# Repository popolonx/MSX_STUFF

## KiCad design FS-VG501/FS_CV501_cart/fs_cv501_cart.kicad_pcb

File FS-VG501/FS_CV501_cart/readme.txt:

kicad files for CV501 cart part.

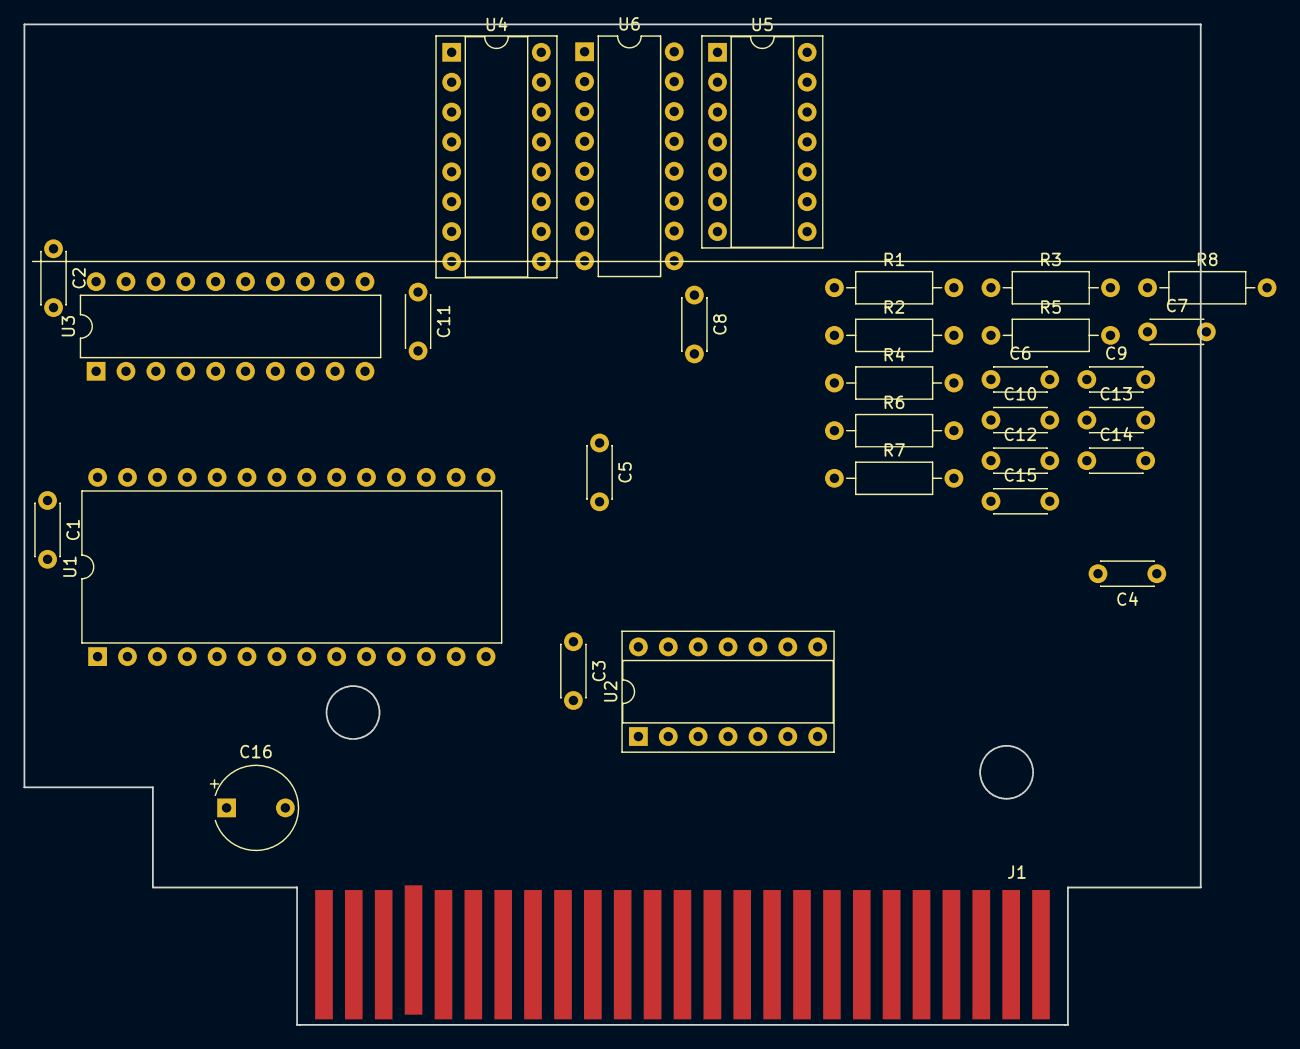
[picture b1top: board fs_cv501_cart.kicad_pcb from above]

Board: 2 copper layers, 100.0 x 85.0 mm, 31 parts (0 on the bottom side), 47 nets, no tracks yet.

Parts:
C1, C2, C3, C4, C5, C8, C11: 100nF; C_Disc_D4.3mm_W1.9mm_P5.00mm
C6, C7, C9, C10, C12, C13, C14, C15: 22p; C_Disc_D4.3mm_W1.9mm_P5.00mm
C16: 100uF; CP_Radial_Tantal_D7.0mm_P5.00mm
J1: Conn_02x25_Odd_Even; msx_cartridge
R1, R2, R3, R4, R5, R6, R7, R8: 1K; R_Axial_DIN0207_L6.3mm_D2.5mm_P10.16mm_Horizontal
U1: TMM27256D-25; DIP-28_W15.24mm
U2: 74LS30; DIP-14_W7.62mm_Socket
U3: 74LS245; DIP-20_W7.62mm
U4: 74LS138; DIP-16_W7.62mm_Socket
U5: 74LS08; DIP-14_W7.62mm_Socket
U6: 74LS367; DIP-16_W7.62mm

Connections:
5V: C1.1, C2.1, C3.1, C4.1, C5.1, C8.1, C11.1, C16.1, J1.45, J1.47, R1.1, R2.1, R3.1, R4.1, R5.1, R6.1, R7.1, R8.1, U1.1, U1.28, U2.14, U3.20, U4.6, U4.16, U5.14, U6.16
A0: J1.28, U1.10, U6.12
A1: J1.27, U1.9, U6.6
A2: J1.30, U1.8
A3: J1.29, U1.7
A4: J1.32, U1.6
A5: J1.31, U1.5
A6: J1.22, U1.4, U2.12
A7: J1.21, U1.3, U2.11
A8: J1.24, U1.25, U2.6
A9: J1.17, U1.24, U2.5
A10: J1.20, U1.21, U2.4
A11: J1.19, U1.23, U2.3
A12: J1.23, U1.2, U2.2
A13: J1.26, U1.26, U2.1
A14: J1.25, U1.27, U4.2
A15: J1.18, U4.3
D0: J1.34, U1.11, U3.2
D1: J1.33, U1.12, U3.3
D2: J1.36, U1.13, U3.4
D3: J1.35, U1.15, U3.5
D4: J1.38, U1.16, U3.6
D5: J1.37, U1.17, U3.7
D6: J1.40, U1.18, U3.8
D7: J1.39, U1.19, U3.9
DB0_PIN1: C6.1, R1.2, U3.18
DB1_PIN2: C7.1, R2.2, U3.17
DB2_PIN3: C9.1, R3.2, U3.16
DB3_PIN4: C10.1, R4.2, U3.15
DB4_PIN5: C12.1, R5.2, U3.14
DB5_PIN6: C13.1, R6.2, U3.13
DB6_PIN7: C14.1, R7.2, U3.12
DB7_PIN8: C15.1, R8.2, U3.11
GND: C1.2, C2.2, C3.2, C4.2, C5.2, C6.2, C7.2, C8.2, C9.2, C10.2, C11.2, C12.2, C13.2, C14.2, C15.2, C16.2, J1.41, J1.43, U1.14, U2.7, U3.10, U4.4, U4.8, U5.7, U6.1, U6.8, U6.15
unnamed: J1.44, J1.46
unnamed: U2.8, U4.1
unnamed: U4.10, U5.2
unnamed: U4.11, U5.4, U6.10
unnamed: U4.12, U5.1
unnamed: U4.13, U5.5, U6.2
_CS12: J1.3, U1.20
_RD: J1.14, U6.4
_RDB_PIN11: U3.1, U6.5
_ROMOE: U1.22, U5.3
_SLTSL: J1.4, U4.5
_SWITCH_ENABLE: U3.19, U5.6
_WR: J1.13, U6.14

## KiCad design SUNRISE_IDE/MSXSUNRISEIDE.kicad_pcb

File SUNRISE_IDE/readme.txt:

sunrise ide module schematics, original can be found from msxpro.com

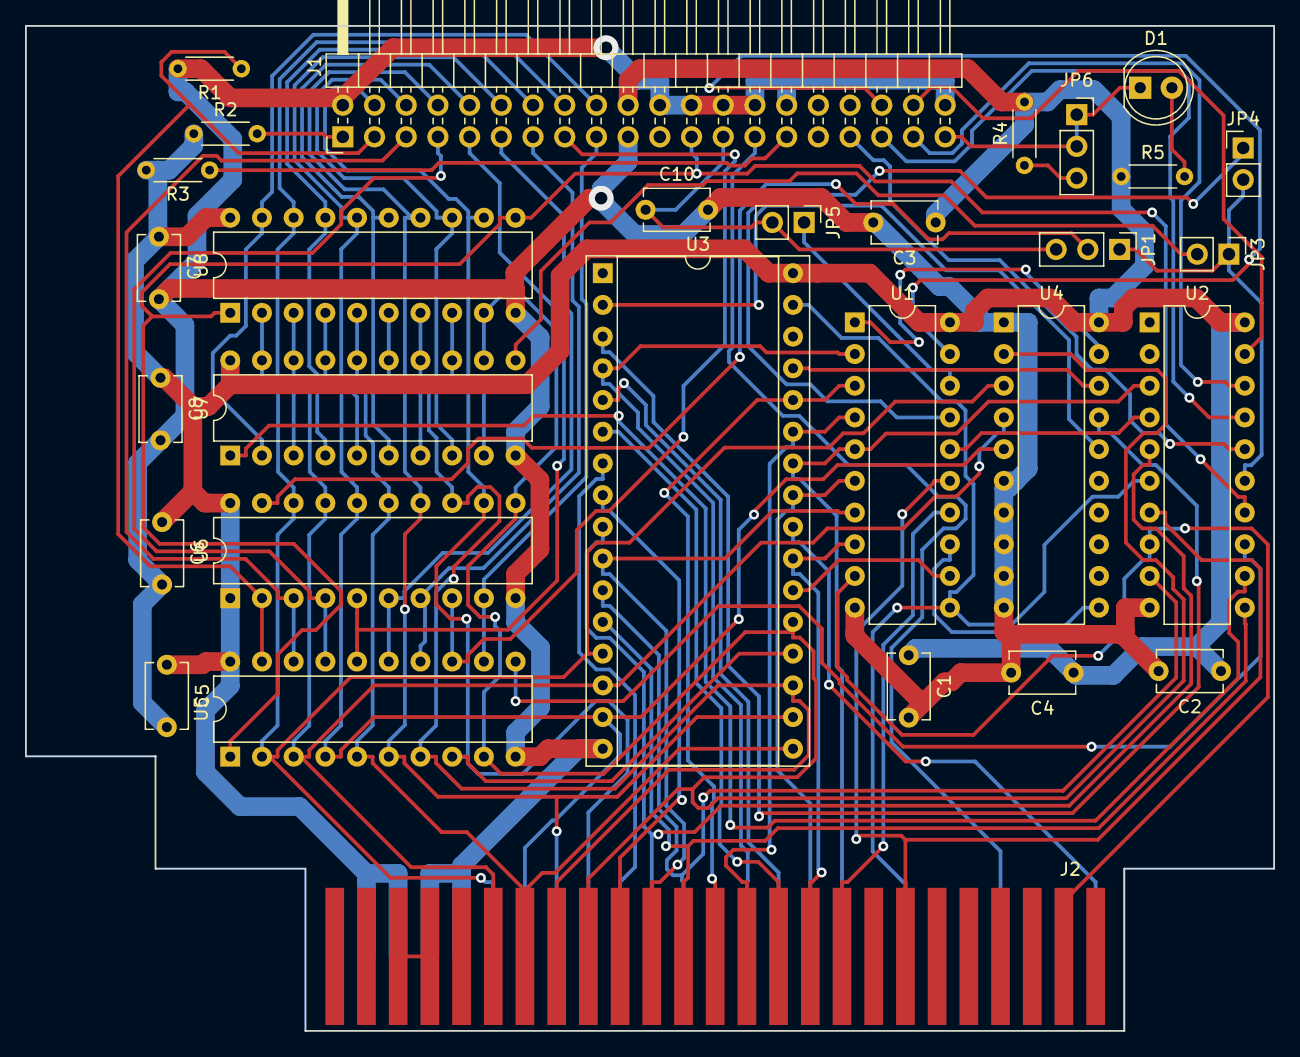
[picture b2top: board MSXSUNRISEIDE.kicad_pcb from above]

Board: 2 copper layers, 100.0 x 80.5 mm, 30 parts (0 on the bottom side), 73 nets.

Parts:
C1, C2, C3, C4, C5: 0.1 uF; C_Disc_D5.1mm_W3.2mm_P5.00mm
C6, C7, C8: 0.1uF; C_Disc_D5.1mm_W3.2mm_P5.00mm
C10: 470pF; C_Disc_D5.1mm_W3.2mm_P5.00mm
D1: LED; LED_D5.0mm
J1: Conn_02x20_Odd_Even; PinHeader_2x20_P2.54mm_Horizontal
J2: Conn_02x25_Odd_Even; msx_cartridge
JP1: Jumper_3_Open; PinHeader_1x03_P2.54mm_Vertical
JP3, JP4, JP5: Jumper; PinHeader_1x02_P2.54mm_Vertical
JP6: Jumper_3_Open; PinSocket_1x03_P2.54mm_Vertical
R1, R3: 10K; R_Axial_DIN0204_L3.6mm_D1.6mm_P5.08mm_Horizontal
R2: 4K7; R_Axial_DIN0204_L3.6mm_D1.6mm_P5.08mm_Horizontal
R4: 330R; R_Axial_DIN0204_L3.6mm_D1.6mm_P5.08mm_Horizontal
R5: 680R; R_Axial_DIN0204_L3.6mm_D1.6mm_P5.08mm_Horizontal
U1, U2: GAL16V8; DIP-20_W7.62mm
U3: SST39SF040; DIP-32_W15.24mm_Socket
U4, U5, U6, U7, U8: 74LS573; DIP-20_W7.62mm

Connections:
A0: J2.28, U2.11, U3.12
A1: J2.27, U2.9, U3.11
A2: J2.30, U1.7, U3.10
A3: J2.29, U2.5, U3.9
A4: J2.32, U3.8
A5: J2.31, U3.7
A6: J2.22, U3.6
A7: J2.21, U3.5
A8: J2.24, U1.4, U3.27
A9: J2.17, U1.5, U2.3, U3.26
A10: J2.20, U1.8, U3.23
A11: J2.19, U1.6, U3.25
A12: J2.23, U1.2, U3.4
A13: J2.26, U1.3, U3.28
A15: J2.18, U1.14
ACTIVE_: D1.1, J1.39, JP6.1, JP6.2
CS1_: J2.1, U3.24
D0: J2.34, U3.21, U4.2, U5.9, U6.11, U7.12, U8.9
D1: J2.33, U3.20, U5.8, U6.12, U7.13, U8.8
D2: J2.36, U3.19, U5.7, U6.13, U7.14, U8.7
D3: J2.35, U3.18, U5.6, U6.14, U7.15, U8.6
D4: J2.38, U3.17, U5.5, U6.15, U7.16, U8.5
D5: J2.37, U3.15, U4.5, U5.4, U6.16, U7.17, U8.4
D6: J2.40, U3.14, U4.4, U5.3, U6.17, U7.18, U8.3
D7: J2.39, U3.13, U4.3, U5.2, U6.18, U7.19, U8.2
DA0: J1.35, U2.17
DA1: J1.33, U2.16
DA2: J1.36, U1.19
DD0: J1.17, U5.12, U6.9
DD1: J1.15, U5.13, U6.8
DD2: J1.13, U5.14, U6.7
DD3: J1.11, U5.15, U6.6
DD4: J1.9, U5.16, U6.5
DD5: J1.7, U5.17, U6.4
DD6: J1.5, U5.18, U6.3
DD7: J1.3, R1.1, U5.19, U6.2
DD8: J1.4, U7.9, U8.12
DD9: J1.6, U7.8, U8.13
DD10: J1.8, U7.7, U8.14
DD11: J1.10, U7.6, U8.15
DD12: J1.12, U7.5, U8.16
DD13: J1.14, U7.4, U8.17
DD14: J1.16, U7.3, U8.18
DD15: J1.18, U7.2, U8.19
D_LOW: JP1.2, U6.19
FLASH_EN_: U1.12, U3.22
GND: C1.2, C2.2, C3.2, C4.2, C5.2, C6.2, C7.2, C8.2, C10.2, J1.2, J1.19, J1.22, J1.24, J1.26, J1.28, J1.30, J1.40, J2.41, J2.43, R1.2, U1.10, U2.10, U3.16, U4.1, U4.6, U4.7, U4.8, U4.9, U4.10, U5.10, U6.10, U7.10, U8.10
IDE_CS0_: J1.37, U2.18
IDE_CS1_: J1.38, U2.19
IOR_: C10.1, J1.25, JP1.3, JP5.2
IOW_: J1.23, U2.14, U5.1, U8.1, U8.11
MA: U1.1, U4.19
MA14: U3.29, U4.18
MA15: U3.3, U4.17
MA16: U3.2, U4.16
NET00003: U2.13, U5.11
unnamed: D1.2, R5.2
unnamed: J1.1, R2.2
unnamed: J1.29, R3.1
unnamed: J2.44, J2.46
unnamed: JP1.1, JP3.1, JP4.2, U2.15
unnamed: JP3.2, U7.11
unnamed: JP4.1, U1.17
unnamed: JP5.1, U1.18
unnamed: JP6.3, R4.1
unnamed: U1.13, U4.11
unnamed: U1.16, U2.4
unnamed: U2.12, U7.1
RD_: J2.14, U1.15, U2.7
SLTSL_: J2.4, U1.9, U2.8
VCC: C1.1, C2.1, C3.1, C4.1, C5.1, C6.1, C7.1, C8.1, J1.20, J2.45, J2.47, R2.1, R3.2, R4.2, R5.1, U1.20, U2.20, U3.32, U4.20, U5.20, U6.1, U6.20, U7.20, U8.20
WAIT_: J1.27, J2.7
WR_: J2.13, U1.11, U2.6, U3.31

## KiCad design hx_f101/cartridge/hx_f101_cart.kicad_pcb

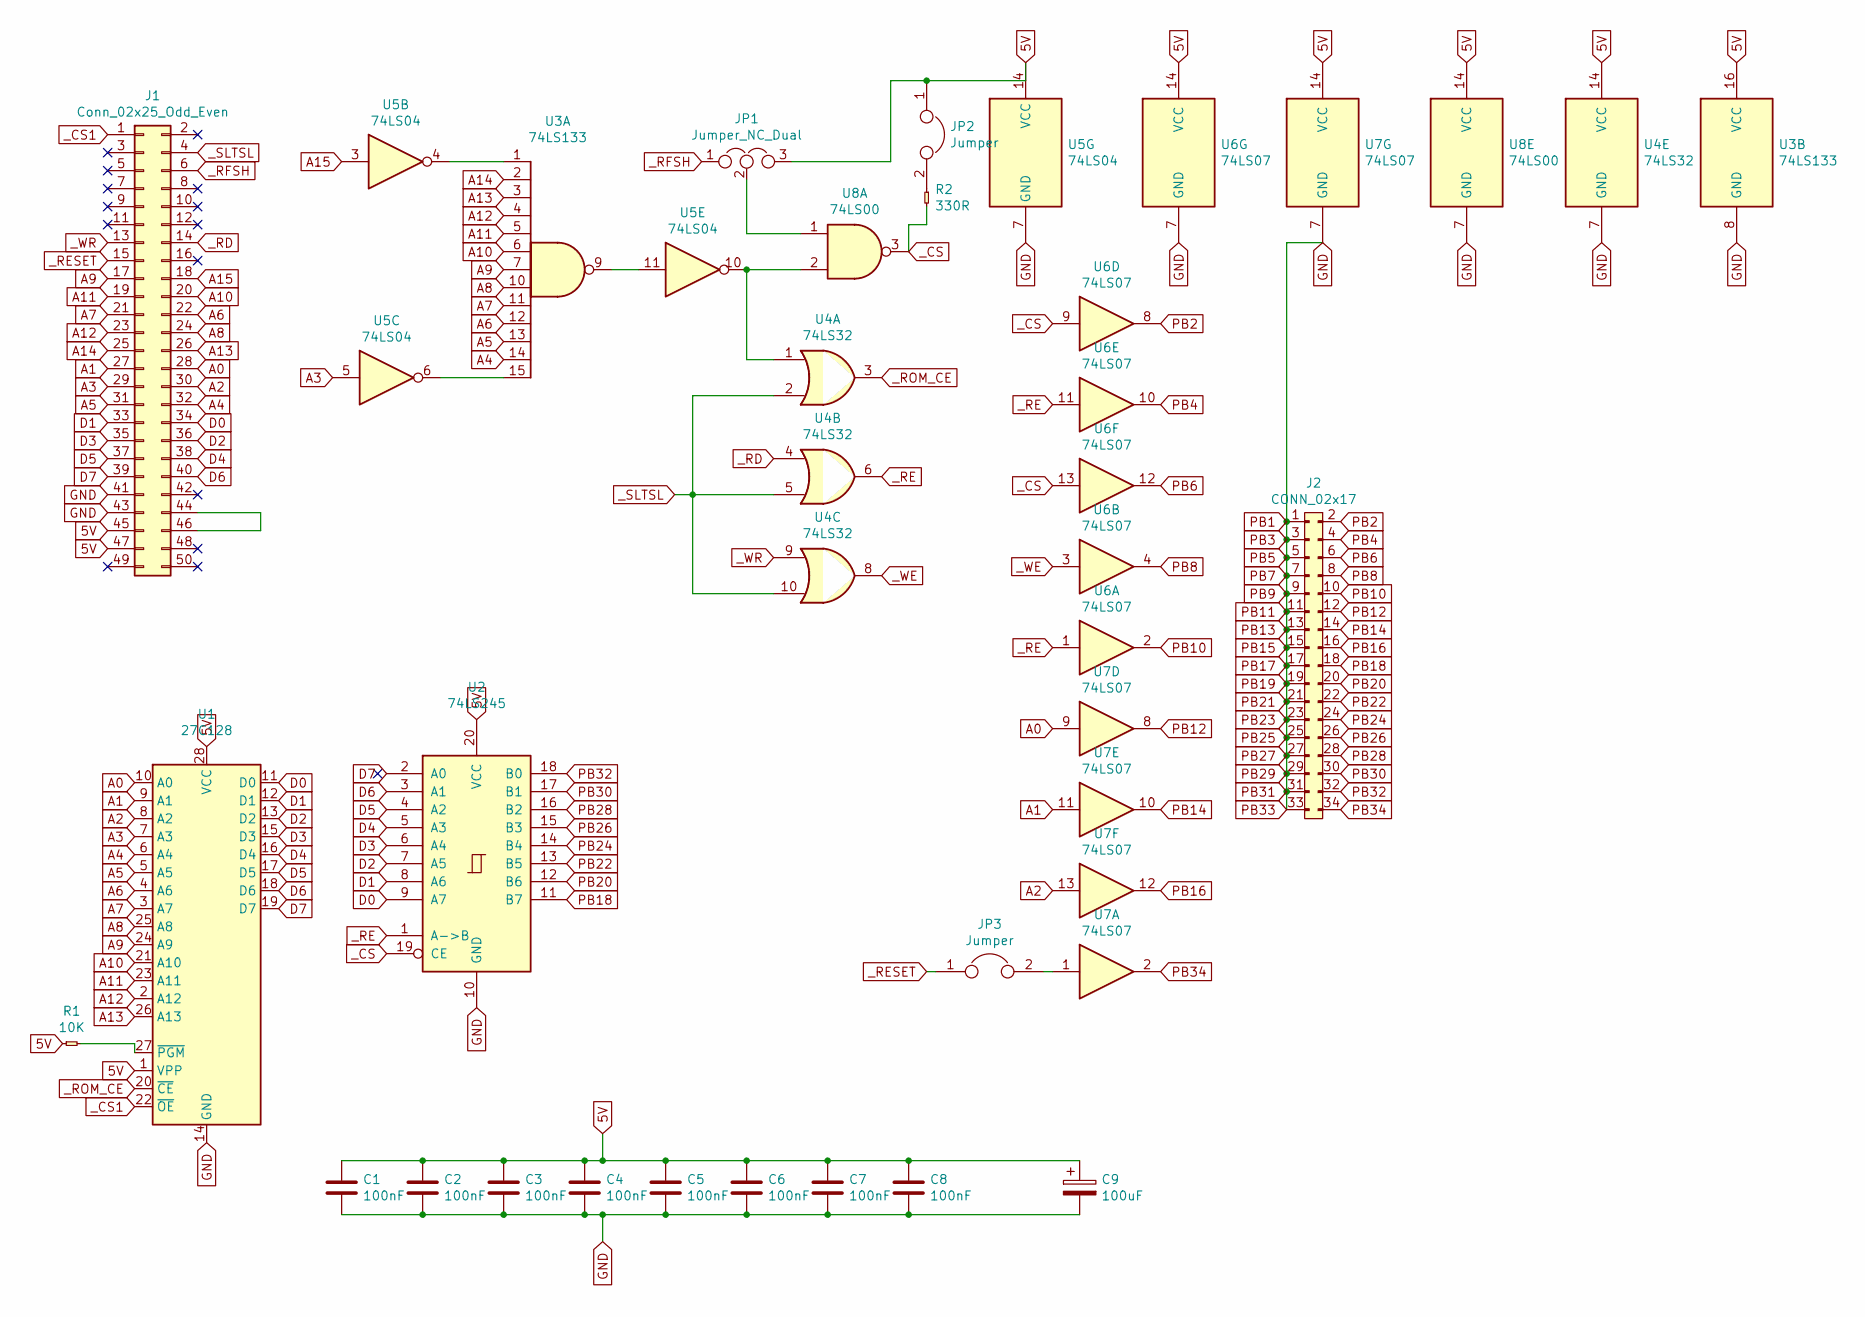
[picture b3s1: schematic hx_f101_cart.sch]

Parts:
C1, C2, C3, C4, C5, C6, C7, C8: 100nF; C_Disc_D4.3mm_W1.9mm_P5.00mm
C9: 100uF; CP_Radial_Tantal_D7.0mm_P5.00mm
J1: Conn_02x25_Odd_Even; msx_cartridge
J2: CONN_02x17; PinHeader_2x17_P2.54mm_Vertical
JP1: Jumper_NC_Dual; PinHeader_1x03_P2.54mm_Vertical
JP2, JP3: Jumper; PinHeader_1x02_P2.54mm_Vertical
R1: 10K; R_Axial_DIN0207_L6.3mm_D2.5mm_P10.16mm_Horizontal
R2: 330R; R_Axial_DIN0207_L6.3mm_D2.5mm_P10.16mm_Horizontal
U1: 27C128; DIP-28_W15.24mm
U2: 74LS245; DIP-20_W7.62mm
U3: 74LS133; DIP-16_W7.62mm
U4: 74LS32; DIP-14_W7.62mm
U5: 74LS04; DIP-14_W7.62mm
U6, U7: 74LS07; DIP-14_W7.62mm
U8: 74LS00; DIP-14_W7.62mm

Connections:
5V: C1.1, C2.1, C3.1, C4.1, C5.1, C6.1, C7.1, C8.1, C9.1, J1.45, J1.47, JP1.3, JP2.1, R1.1, U1.1 (VPP), U1.28 (VCC), U2.20 (VCC), U3.16 (VCC), U4.14 (VCC), U5.14 (VCC), U6.14 (VCC), U7.14 (VCC), U8.14 (VCC)
A0: J1.28, U1.10 (A0), U7.9
A1: J1.27, U1.9 (A1), U7.11
A2: J1.30, U1.8 (A2), U7.13
A3: J1.29, U1.7 (A3), U5.5
A4: J1.32, U1.6 (A4), U3.14
A5: J1.31, U1.5 (A5), U3.13
A6: J1.22, U1.4 (A6), U3.12
A7: J1.21, U1.3 (A7), U3.11
A8: J1.24, U1.25 (A8), U3.10
A9: J1.17, U1.24 (A9), U3.7
A10: J1.20, U1.21 (A10), U3.6
A11: J1.19, U1.23 (A11), U3.5
A12: J1.23, U1.2 (A12), U3.4
A13: J1.26, U1.26 (A13), U3.3
A14: J1.25, U3.2
A15: J1.18, U5.3
D0: J1.34, U1.11 (D0), U2.9 (A7)
D1: J1.33, U1.12 (D1), U2.8 (A6)
D2: J1.36, U1.13 (D2), U2.7 (A5)
D3: J1.35, U1.15 (D3), U2.6 (A4)
D4: J1.38, U1.16 (D4), U2.5 (A3)
D5: J1.37, U1.17 (D5), U2.4 (A2)
D6: J1.40, U1.18 (D6), U2.3 (A1)
D7: J1.39, U1.19 (D7), U2.2 (A0)
GND: C1.2, C2.2, C3.2, C4.2, C5.2, C6.2, C7.2, C8.2, C9.2, J1.41, J1.43, J2.1, J2.3, J2.5, J2.7, J2.9, J2.11, J2.13, J2.15, J2.17, J2.19, J2.21, J2.23, J2.25, J2.27, J2.29, J2.31, J2.33, U1.14 (GND), U2.10 (GND), U3.8 (GND), U4.7 (GND), U5.7 (GND), U6.7 (GND), U7.7 (GND), U8.7 (GND)
unnamed: J1.44, J1.46
unnamed: JP1.2, U8.1
unnamed: JP2.2, R2.1
unnamed: JP3.2, U7.1
unnamed: R1.2, U1.27 (~PGM)
unnamed: U3.1, U5.4
unnamed: U3.9, U5.11
unnamed: U3.15, U5.6
unnamed: U4.1, U5.10, U8.2
PB2: J2.2, U6.8
PB4: J2.4, U6.10
PB6: J2.6, U6.12
PB8: J2.8, U6.4
PB10: J2.10, U6.2
PB12: J2.12, U7.8
PB14: J2.14, U7.10
PB16: J2.16, U7.12
PB18: J2.18, U2.11 (B7)
PB20: J2.20, U2.12 (B6)
PB22: J2.22, U2.13 (B5)
PB24: J2.24, U2.14 (B4)
PB26: J2.26, U2.15 (B3)
PB28: J2.28, U2.16 (B2)
PB30: J2.30, U2.17 (B1)
PB32: J2.32, U2.18 (B0)
PB34: J2.34, U7.2
_CS: R2.2, U2.19 (CE), U6.9, U6.13, U8.3
_CS1: J1.1, U1.22 (~OE)
_RD: J1.14, U4.4
_RE: U2.1 (A->B), U4.6, U6.1, U6.11
_RESET: J1.15, JP3.1
_RFSH: J1.6, JP1.1
_ROM_CE: U1.20 (~CE), U4.3
_SLTSL: J1.4, U4.2, U4.5, U4.10
_WE: U4.8, U6.3
_WR: J1.13, U4.9

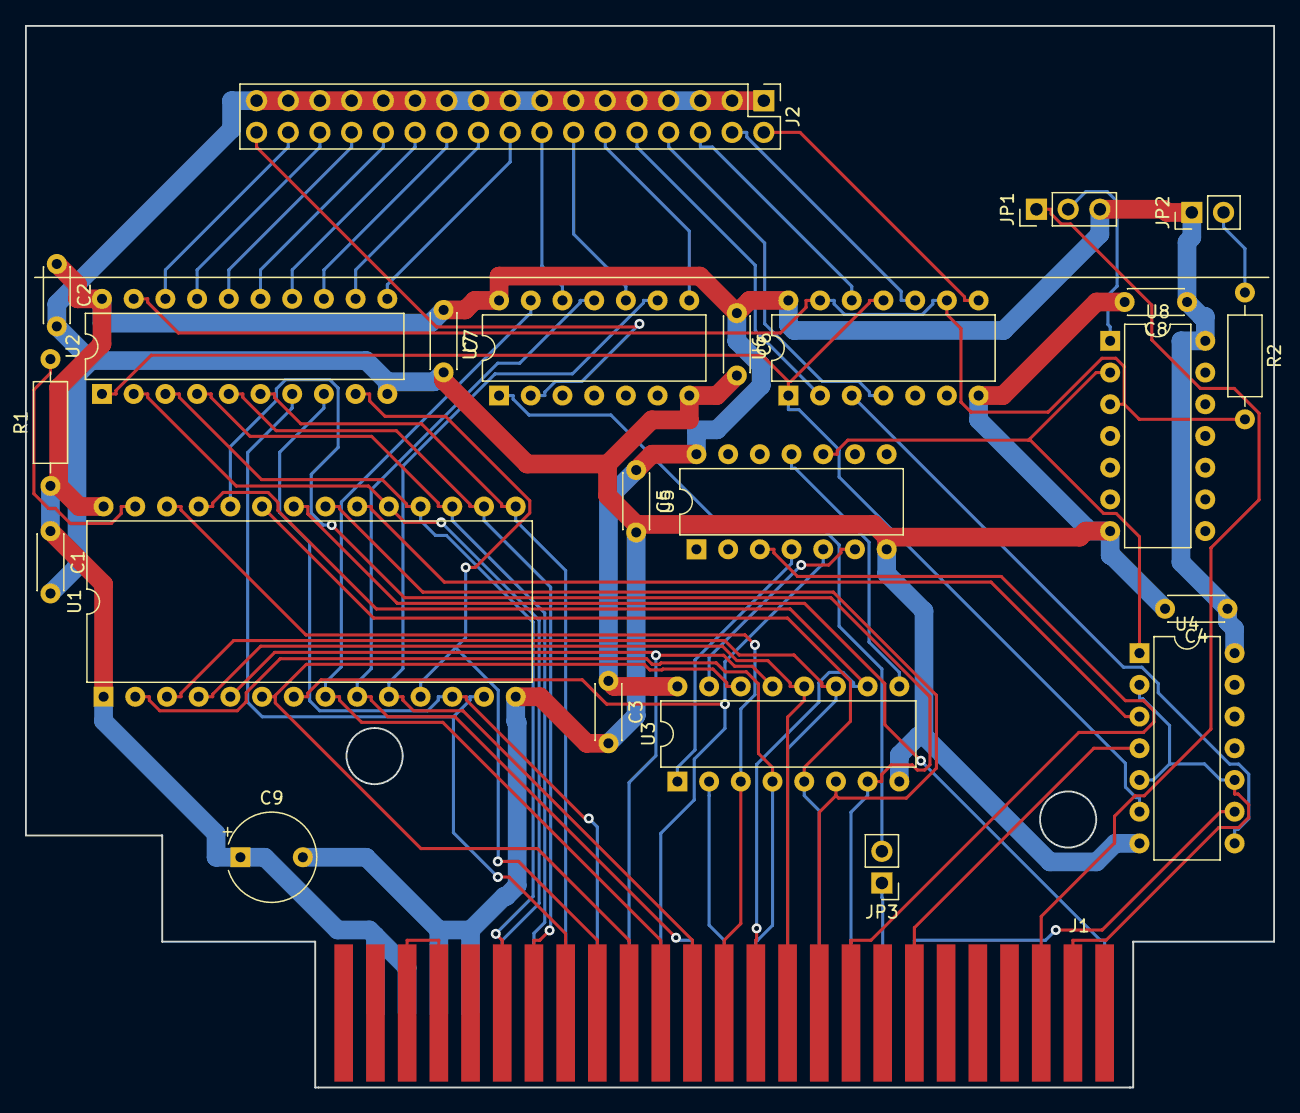
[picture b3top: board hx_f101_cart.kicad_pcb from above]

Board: 2 copper layers, 100.0 x 85.0 mm, 24 parts (0 on the bottom side), 62 nets.

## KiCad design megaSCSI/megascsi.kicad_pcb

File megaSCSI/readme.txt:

MegaSCSI kicad files.
NOTE! The design has not been tested yet.
NOTE! import footprint libraries from footprint directory.

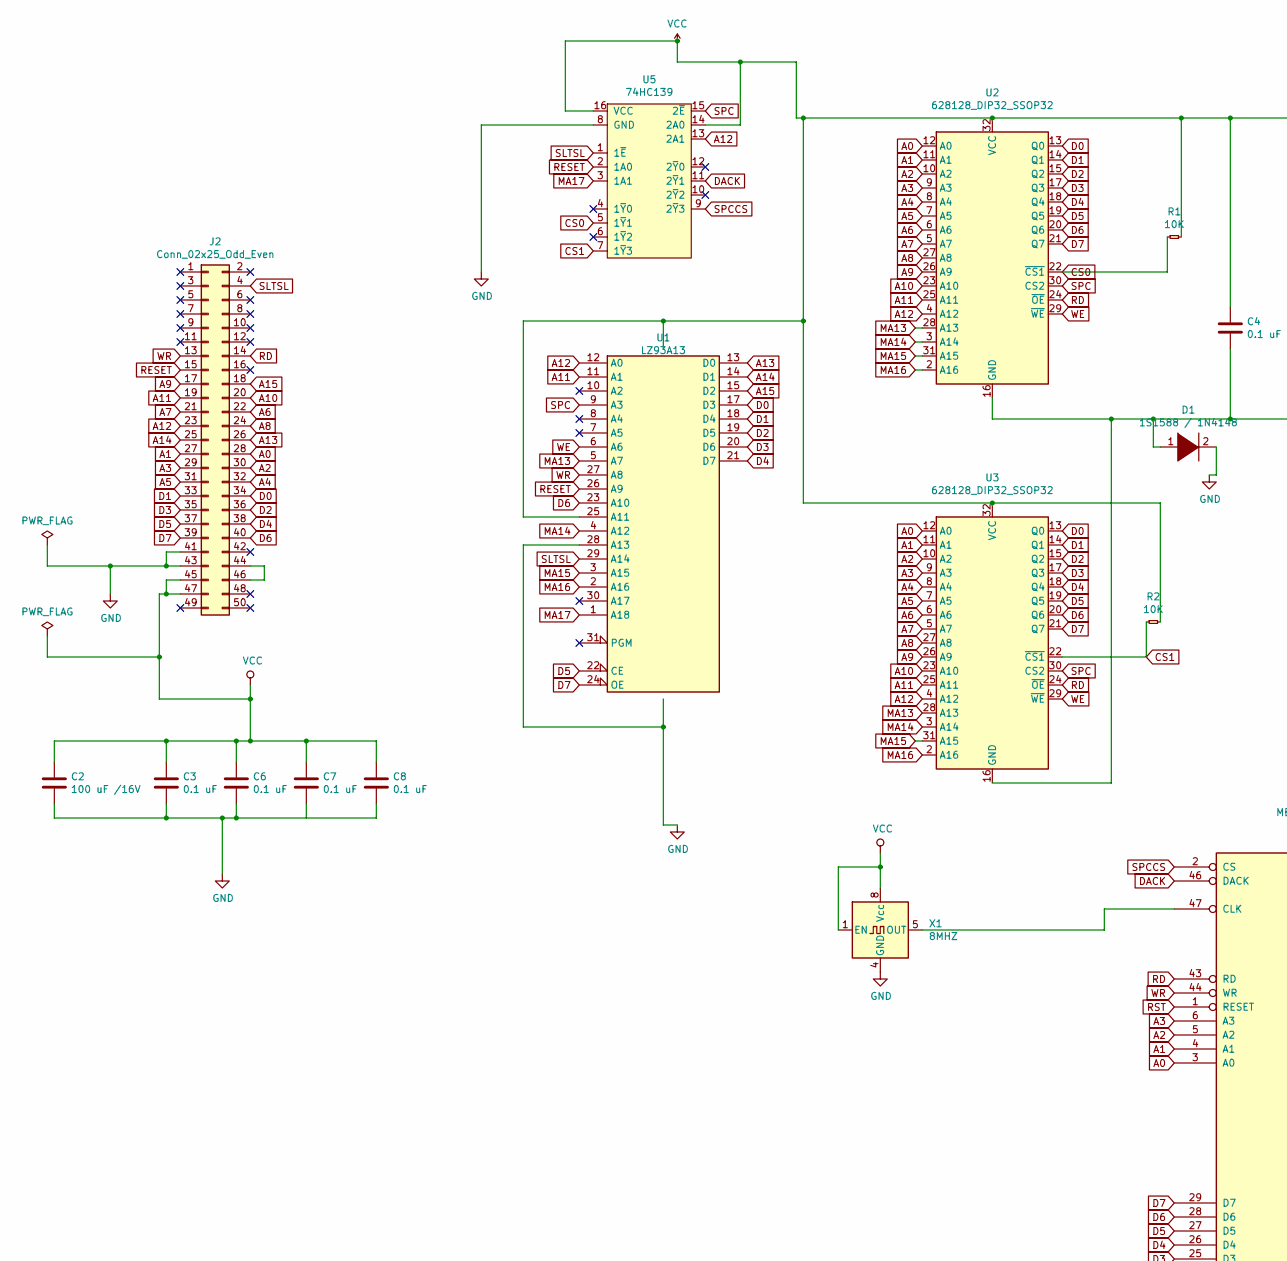
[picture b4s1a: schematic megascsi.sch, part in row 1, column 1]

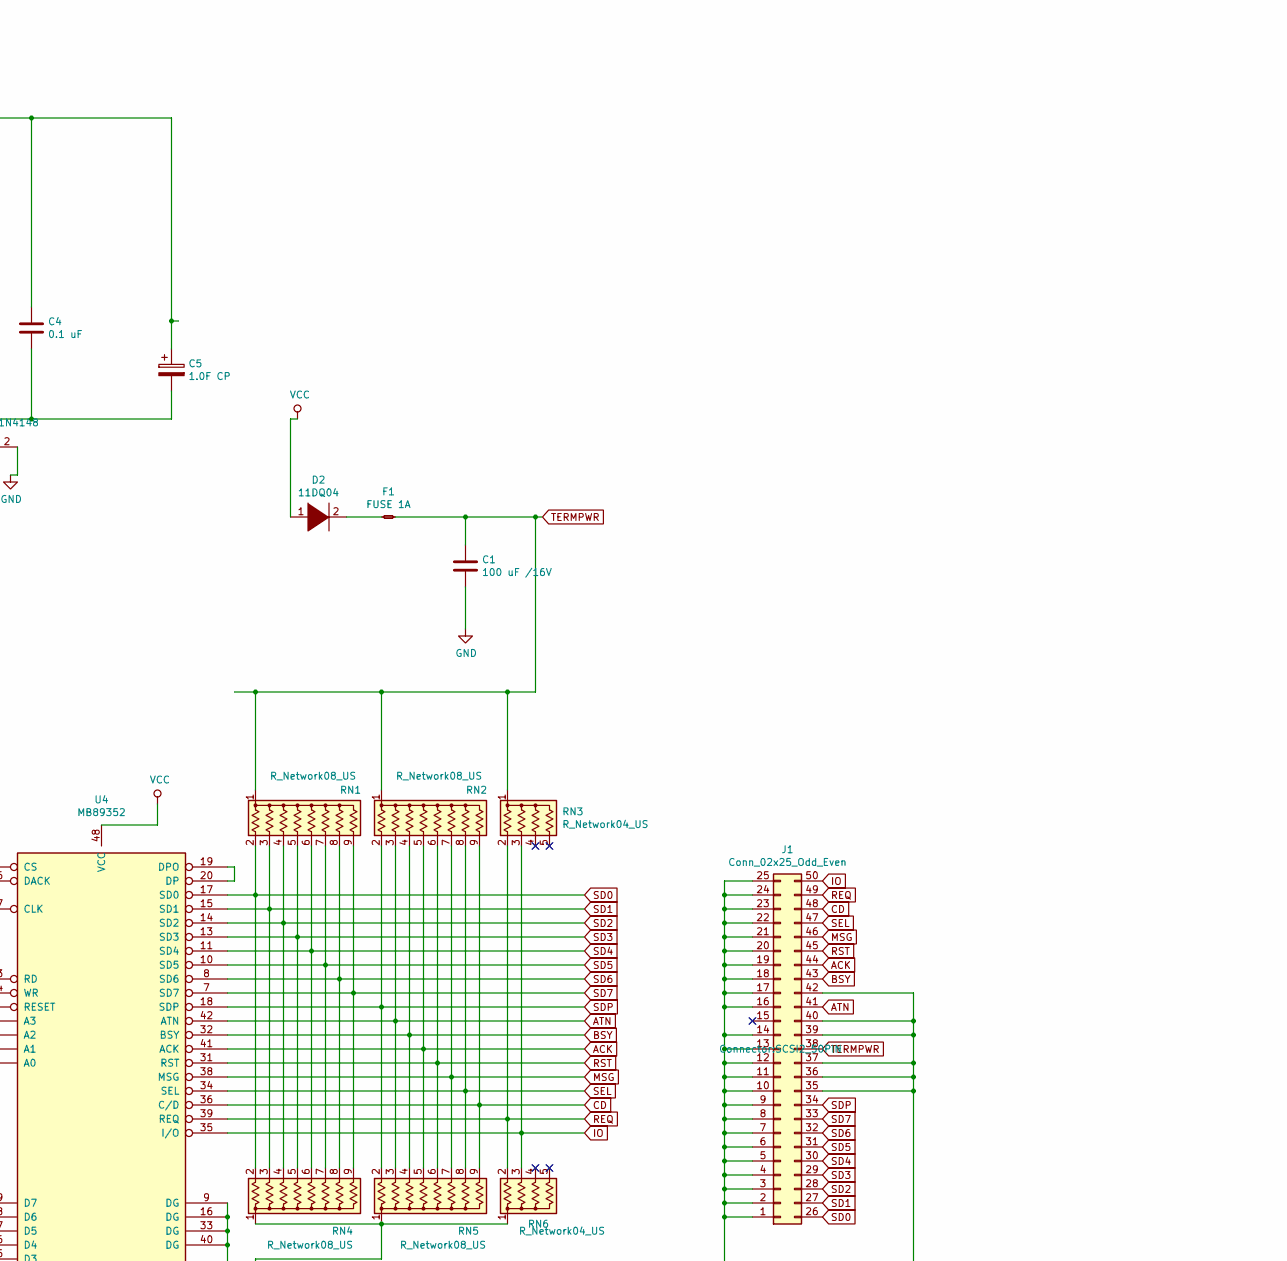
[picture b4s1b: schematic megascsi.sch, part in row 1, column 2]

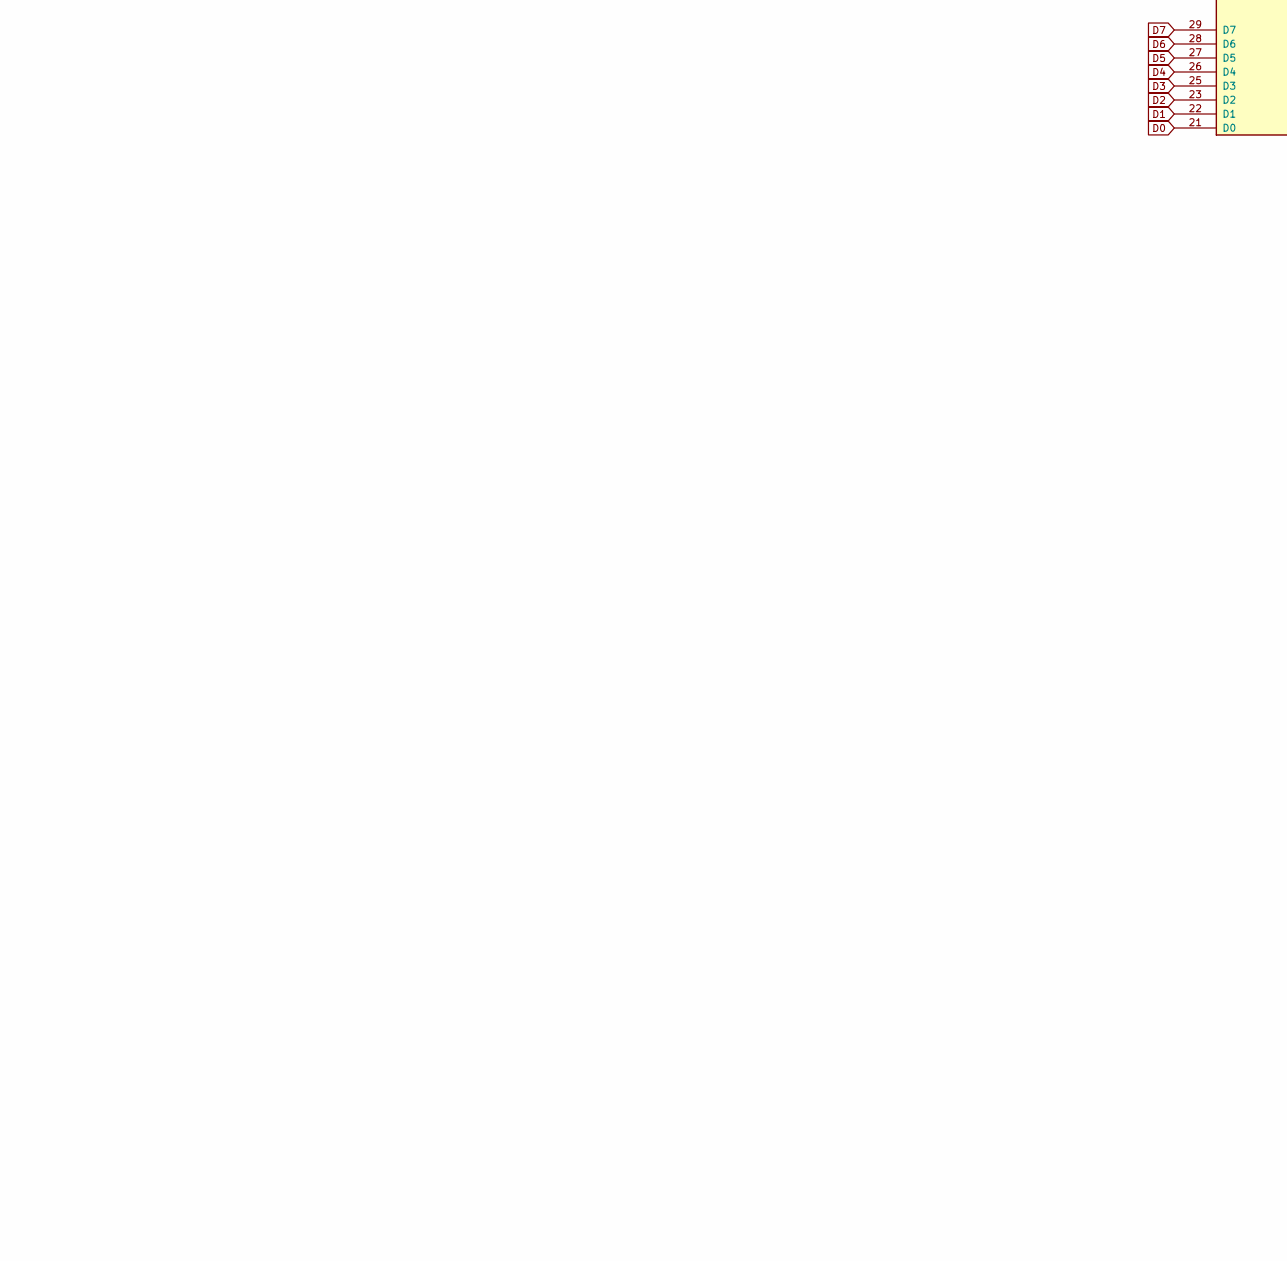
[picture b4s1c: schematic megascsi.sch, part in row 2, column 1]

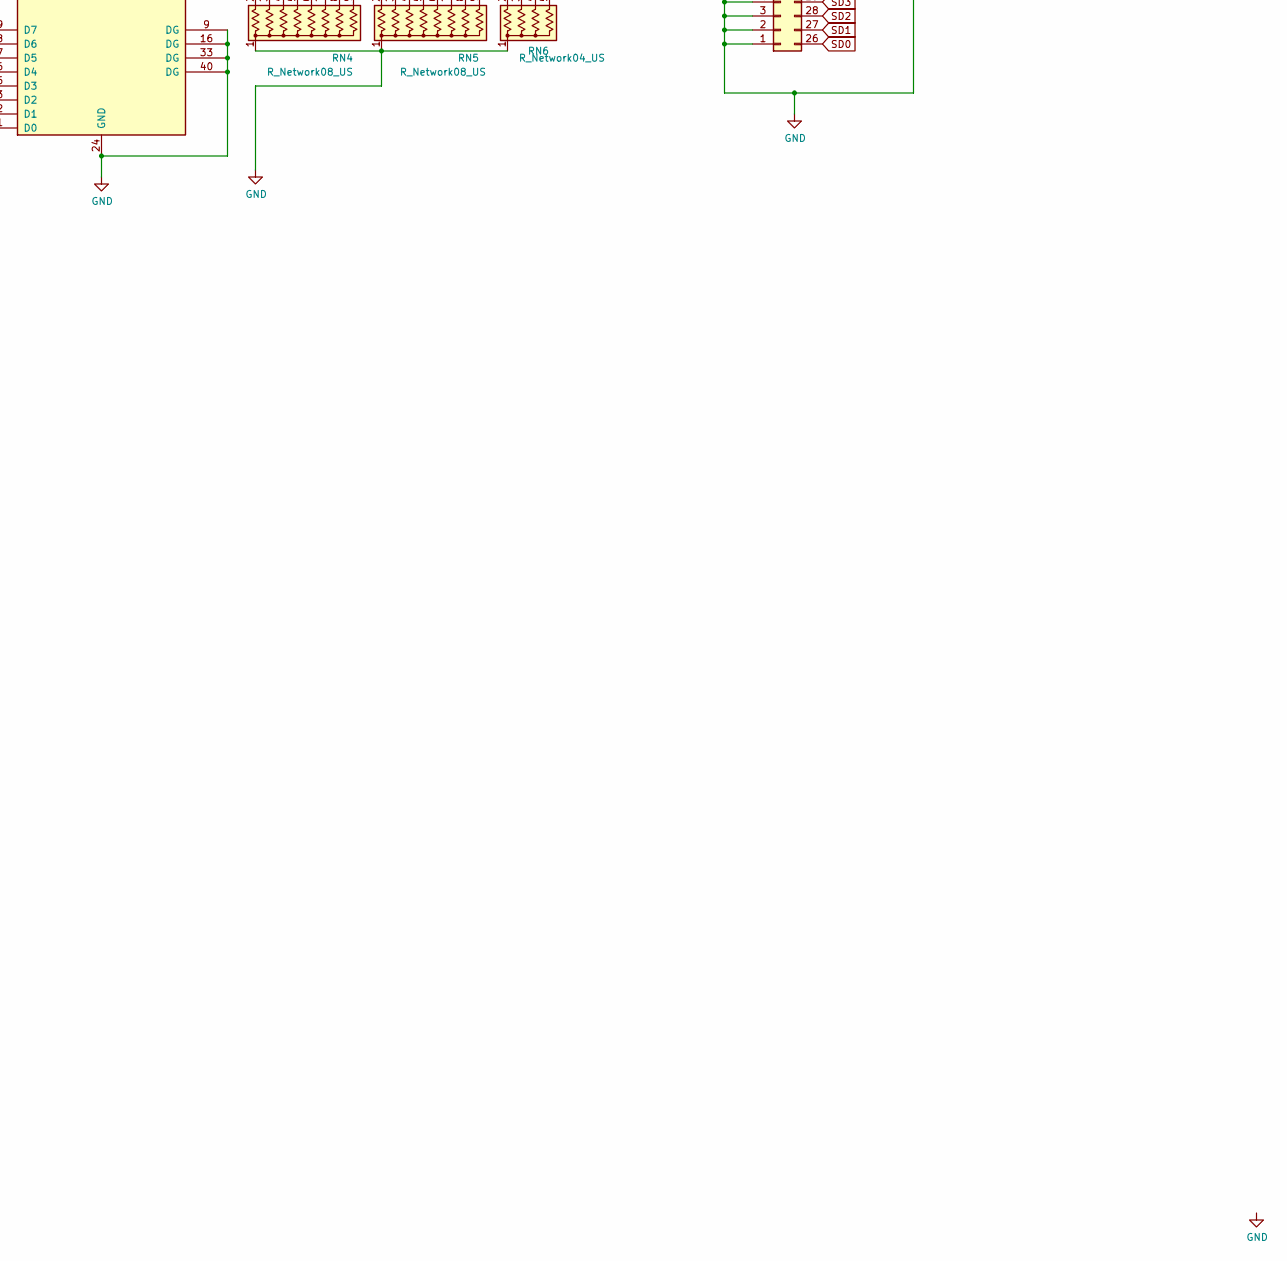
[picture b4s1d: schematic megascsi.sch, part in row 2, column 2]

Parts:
C1, C2: 100 uF /16V; C_Radial_D6.3mm_H7.0mm_P2.50mm
C3, C4, C6, C7, C8: 0.1 uF; C_Disc_D5.1mm_W3.2mm_P5.00mm
C5: 1.0F CP; CP_Radial_Tantal_D5.5mm_P5.00mm
D1: 1S1588 / 1N4148; D_A-405_P7.62mm_Horizontal
D2: 11DQ04; D_A-405_P7.62mm_Horizontal
F1: FUSE 1A; Fuse_BelFuse_0ZRE0005FF_L8.3mm_W3.8mm
J1: Conn_02x25_Odd_Even; SCSI2_50PIN
J2: Conn_02x25_Odd_Even; msx_cartridge
R1, R2: 10K; R_Axial_DIN0309_L9.0mm_D3.2mm_P2.54mm_Vertical
RN1, RN2, RN4, RN5: R_Network08_US; R_Array_SIP9
RN3, RN6: R_Network04_US; R_Array_SIP5
U1: LZ93A13; DIP-32_W15.24mm_LongPads
U2, U3: 628128_DIP32_SSOP32; DIP-32_W15.24mm_LongPads
U4: MB89352; DIP-48_W15.24mm_Socket_LongPads
U5: 74HC139; DIP-16_W7.62mm_Socket_LongPads; Farnell 2444981
X1: 8MHZ; Oscillator_DIP-8

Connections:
A0: J2.28, U2.12 (A0), U3.12 (A0), U4.3 (A0)
A1: J2.27, U2.11 (A1), U3.11 (A1), U4.4 (A1)
A2: J2.30, U2.10 (A2), U3.10 (A2), U4.5 (A2)
A3: J2.29, U2.9 (A3), U3.9 (A3), U4.6 (A3)
A4: J2.32, U2.8 (A4), U3.8 (A4)
A5: J2.31, U2.7 (A5), U3.7 (A5)
A6: J2.22, U2.6 (A6), U3.6 (A6)
A7: J2.21, U2.5 (A7), U3.5 (A7)
A8: J2.24, U2.27 (A8), U3.27 (A8)
A9: J2.17, U2.26 (A9), U3.26 (A9)
A10: J2.20, U2.23 (A10), U3.23 (A10)
A11: J2.19, U1.11 (A1), U2.25 (A11), U3.25 (A11)
A12: J2.23, U1.12 (A0), U2.4 (A12), U3.4 (A12), U5.13 (2A1)
A13: J2.26, U1.13 (D0)
A14: J2.25, U1.14 (D1)
A15: J2.18, U1.15 (D2)
ACK: J1.44, RN2.5 (R4), RN5.5 (R4), U4.41 (ACK)
ATN: J1.41, RN2.3 (R2), RN5.3 (R2), U4.42 (ATN)
BSY: J1.43, RN2.4 (R3), RN5.4 (R3), U4.32 (BSY)
CD: J1.48, RN2.9 (R8), RN5.9 (R8), U4.36 (C/D)
CS0: R1.1, U2.22 (~CS1), U5.5 (1~Y~1)
CS1: R2.1, U3.22 (~CS1), U5.7 (1~Y~3)
D0: J2.34, U1.17 (D3), U2.13 (Q0), U3.13 (Q0), U4.21 (D0)
D1: J2.33, U1.18 (D4), U2.14 (Q1), U3.14 (Q1), U4.22 (D1)
D2: J2.36, U1.19 (D5), U2.15 (Q2), U3.15 (Q2), U4.23 (D2)
D3: J2.35, U1.20 (D6), U2.17 (Q3), U3.17 (Q3), U4.25 (D3)
D4: J2.38, U1.21 (D7), U2.18 (Q4), U3.18 (Q4), U4.26 (D4)
D5: J2.37, U1.22 (CE), U2.19 (Q5), U3.19 (Q5), U4.27 (D5)
D6: J2.40, U1.23 (A10), U2.20 (Q6), U3.20 (Q6), U4.28 (D6)
D7: J2.39, U1.24 (OE), U2.21 (Q7), U3.21 (Q7), U4.29 (D7)
DACK: U4.46 (DACK), U5.11 (2~Y~1)
GND: C1.2, C2.2, C3.2, C6.2, C7.2, C8.2, D1.2 (A), J1.1, J1.2, J1.3, J1.4, J1.5, J1.6, J1.7, J1.8, J1.9, J1.10, J1.11, J1.12, J1.13, J1.14, J1.16, J1.17, J1.18, J1.19, J1.20, J1.21, J1.22, J1.23, J1.24, J1.25, J1.35, J1.36, J1.37, J1.39, J1.40, J1.42, J2.41, J2.43, RN4.1 (common), RN5.1 (common), RN6.1 (common), U1.16 (GND), U1.28 (A13), U4.9 (DG), U4.16 (DG), U4.24 (GND), U4.33 (DG), U4.40 (DG), U5.8 (GND), X1.4 (GND)
IO: J1.50, RN3.3 (R2), RN6.3 (R2), U4.35 (I/O)
MA13: U1.5 (A7), U2.28 (A13), U3.28 (A13)
MA14: U1.4 (A12), U2.3 (A14), U3.3 (A14)
MA15: U1.3 (A15), U2.31 (A15), U3.31 (A15)
MA16: U1.2 (A16), U2.2 (A16), U3.2 (A16)
MA17: U1.1 (A18), U5.3 (1A1)
MSG: J1.46, RN2.7 (R6), RN5.7 (R6), U4.38 (MSG)
unnamed: C4.2, C5.2, D1.1 (K), U2.16 (GND), U3.16 (GND)
unnamed: D2.2 (A), F1.1
unnamed: J2.44, J2.46
unnamed: U4.19 (DPO), U4.20 (DP)
unnamed: U4.47 (CLK), X1.5 (OUT)
RD: J2.14, U2.24 (~OE), U3.24 (~OE), U4.43 (RD)
REQ: J1.49, RN3.2 (R1), RN6.2 (R1), U4.39 (REQ)
RESET: J2.15, U1.26 (A9), U5.2 (1A0)
RST: J1.45, RN2.6 (R5), RN5.6 (R5), U4.1 (RESET), U4.31 (RST)
SD0: J1.26, RN1.2 (R1), RN4.2 (R1), U4.17 (SD0)
SD1: J1.27, RN1.3 (R2), RN4.3 (R2), U4.15 (SD1)
SD2: J1.28, RN1.4 (R3), RN4.4 (R3), U4.14 (SD2)
SD3: J1.29, RN1.5 (R4), RN4.5 (R4), U4.13 (SD3)
SD4: J1.30, RN1.6 (R5), RN4.6 (R5), U4.11 (SD4)
SD5: J1.31, RN1.7 (R6), RN4.7 (R6), U4.10 (SD5)
SD6: J1.32, RN1.8 (R7), RN4.8 (R7), U4.8 (SD6)
SD7: J1.33, RN1.9 (R8), RN4.9 (R8), U4.7 (SD7)
SDP: J1.34, RN2.2 (R1), RN5.2 (R1), U4.18 (SDP)
SEL: J1.47, RN2.8 (R7), RN5.8 (R7), U4.34 (SEL)
SLTSL: J2.4, U1.29 (A14), U5.1 (1~E)
SPC: U1.9 (A3), U2.30 (CS2), U3.30 (CS2), U5.15 (2~E)
SPCCS: U4.2 (CS), U5.9 (2~Y~3)
TERMPWR: C1.1, F1.2, J1.38, RN1.1 (common), RN2.1 (common), RN3.1 (common)
VCC: C2.1, C3.1, C4.1, C5.1, C6.1, C7.1, C8.1, D2.1 (K), J2.45, J2.47, R1.2, R2.2, U1.25 (A11), U1.32 (VCC), U2.32 (VCC), U3.32 (VCC), U4.48 (VCC), U5.14 (2A0), U5.16 (VCC), X1.1 (EN), X1.8 (Vcc)
WE: U1.6 (A6), U2.29 (~WE), U3.29 (~WE)
WR: J2.13, U1.27 (A8), U4.44 (WR)

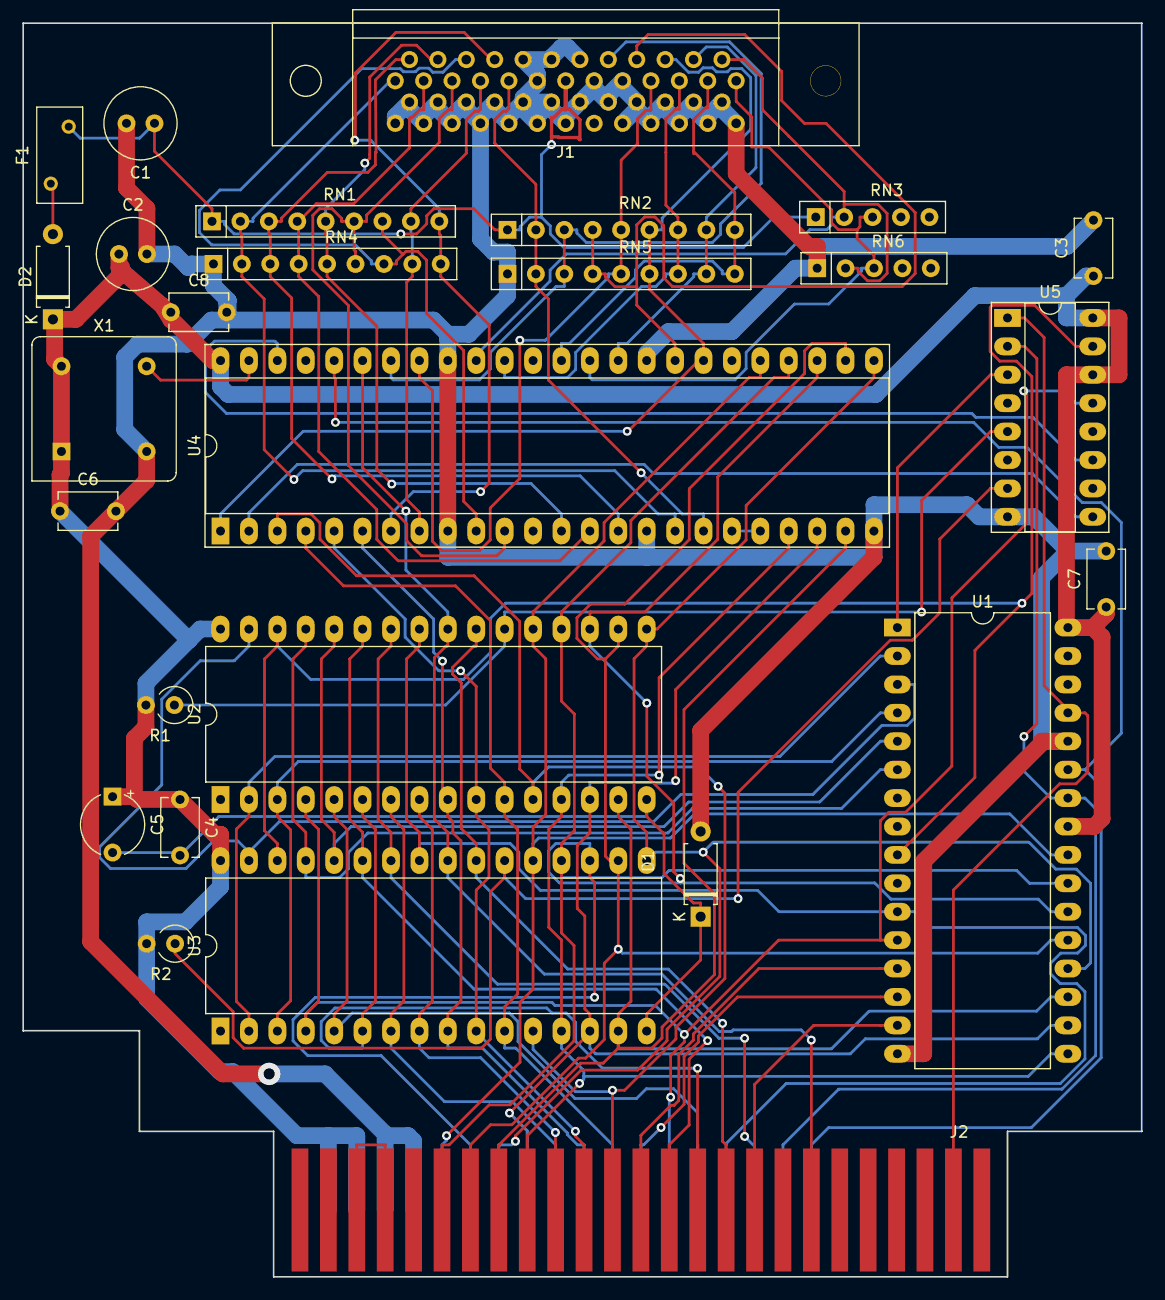
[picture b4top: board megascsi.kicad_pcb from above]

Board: 2 copper layers, 100.0 x 112.1 mm, 27 parts (0 on the bottom side), 65 nets.
